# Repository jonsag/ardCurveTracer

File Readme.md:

# Transistor Curve Tracer

Based on a project I found at [instructables](https://www.instructables.com/Transistor-Curve-Tracer)

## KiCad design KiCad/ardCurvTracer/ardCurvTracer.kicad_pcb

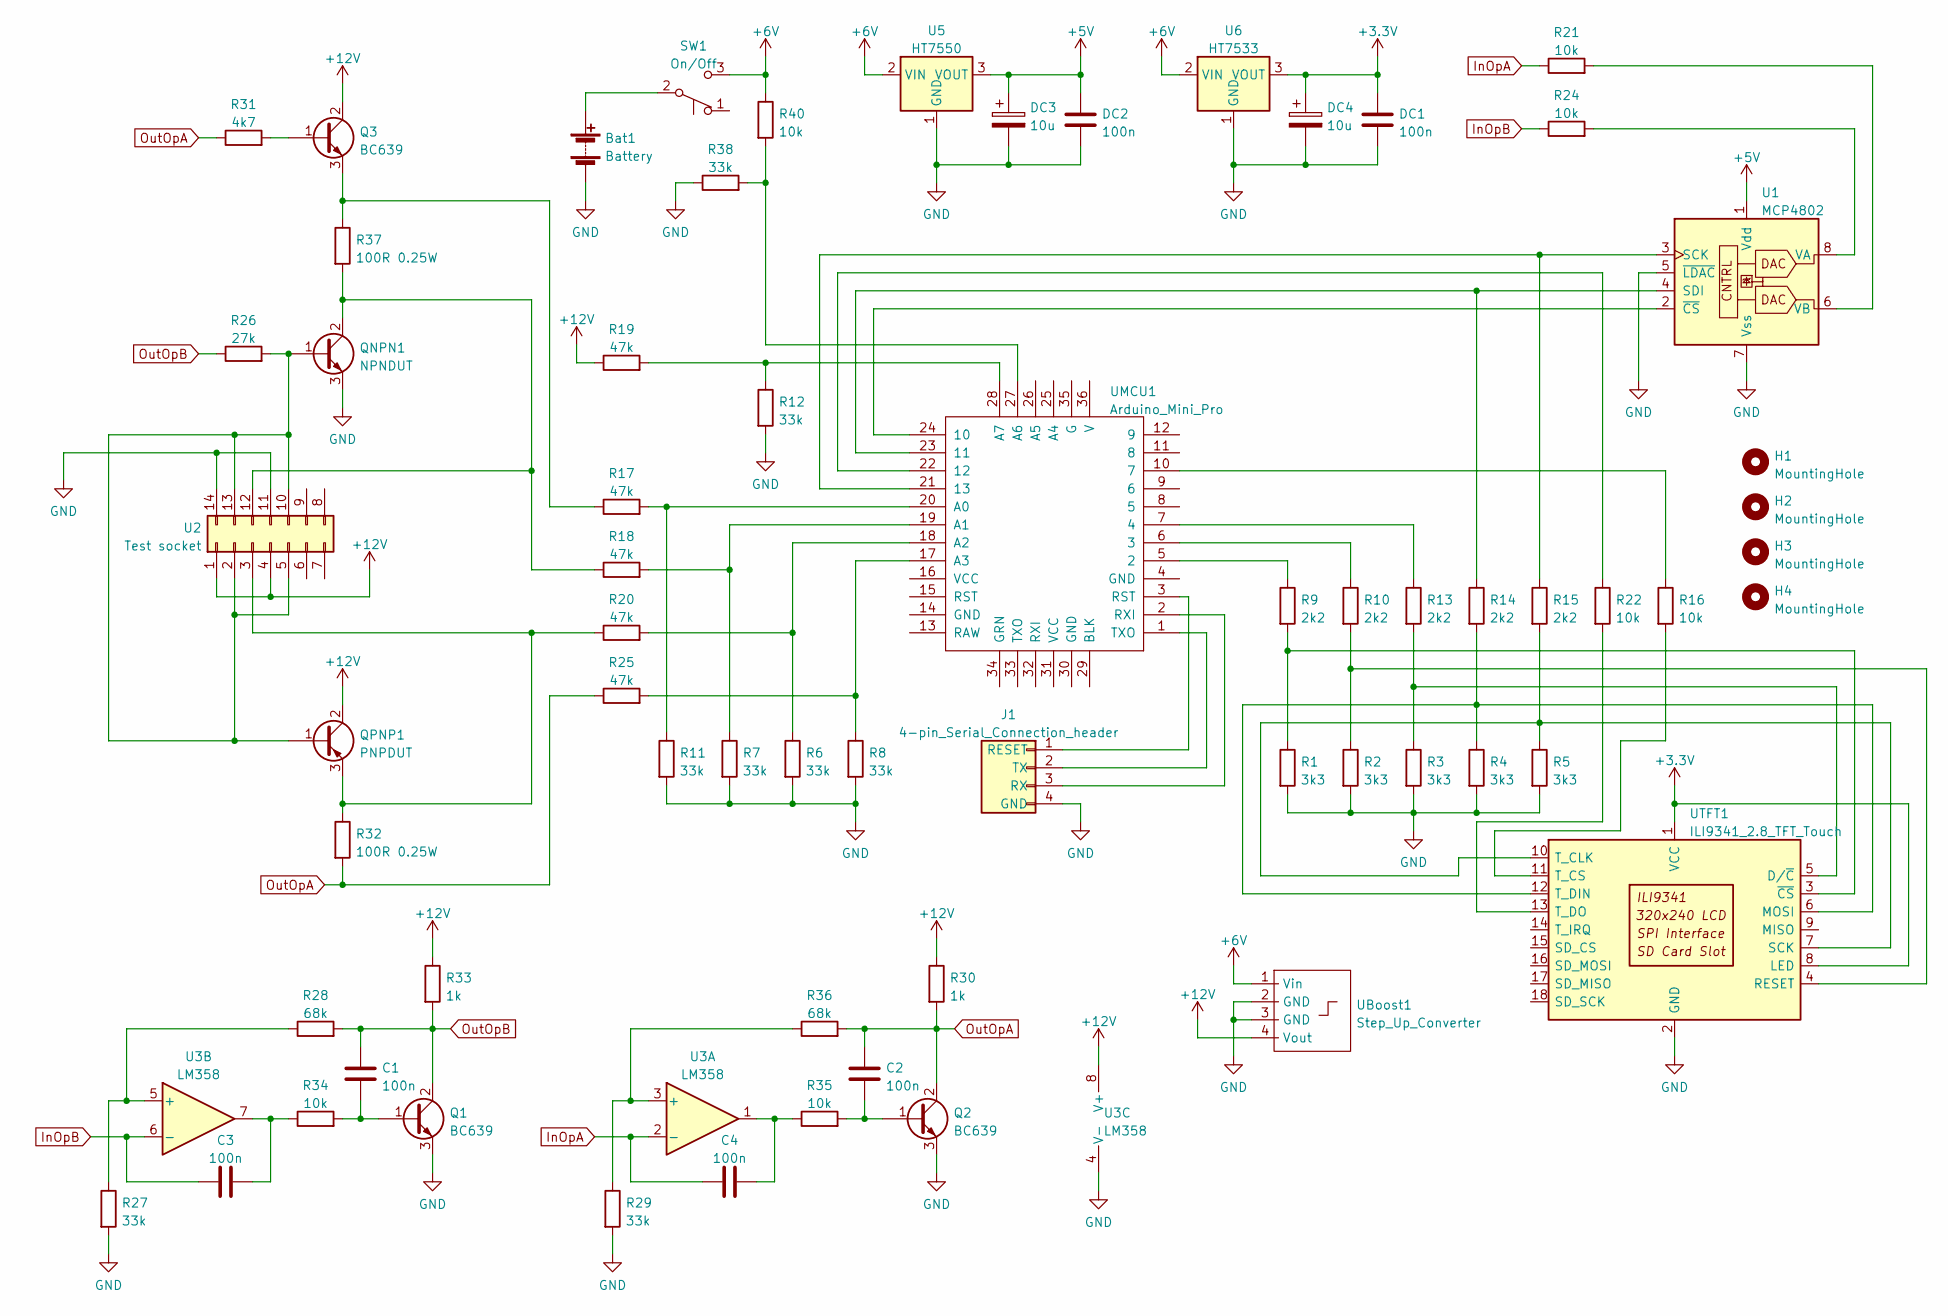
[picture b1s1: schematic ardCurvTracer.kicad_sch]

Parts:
Bat1: Battery; 2-pin_power_input_header_larger_pads
C1, C2, C3, C4: 100n; C_Disc_D3.0mm_W1.6mm_P2.50mm_larg
DC1, DC2: 100n; C_Disc_D3.0mm_W1.6mm_P2.50mm_larg
DC3, DC4: 10u; CP_Radial_D5.0mm_P2.00mm_larger
H1, H2, H3, H4: MountingHole; MountingHole_3.2mm_M3
J1: 4-pin_Serial_Connection_header; 4-pin Serial Connection header large
Q1, Q2, Q3: BC639; TO-92_Inline_Wide_large
QNPN1: NPNDUT
QPNP1: PNPDUT
R1, R2, R3, R4, R5: 3k3; R_Axial_DIN0207_L6.3mm_D2.5mm_P10.16mm_Horizontal_larger_pa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
R6, R7, R8, R11, R12, R27, R29, R38: 33k; R_Axial_DIN0207_L6.3mm_D2.5mm_P10.16mm_Horizontal_larger_pa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
R9, R10, R13, R14, R15: 2k2; R_Axial_DIN0207_L6.3mm_D2.5mm_P10.16mm_Horizontal_larger_pa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
R16, R21, R22, R24, R34, R35, R40: 10k; R_Axial_DIN0207_L6.3mm_D2.5mm_P10.16mm_Horizontal_larger_pa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
R17, R18, R19, R20, R25: 47k; R_Axial_DIN0207_L6.3mm_D2.5mm_P10.16mm_Horizontal_larger_pa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
R26: 27k; R_Axial_DIN0207_L6.3mm_D2.5mm_P10.16mm_Horizontal_larger_pa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
R28, R36: 68k; R_Axial_DIN0207_L6.3mm_D2.5mm_P10.16mm_Horizontal_larger_pa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
R30, R33: 1k; R_Axial_DIN0207_L6.3mm_D2.5mm_P10.16mm_Horizontal_larger_pa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
R31: 4k7; R_Axial_DIN0207_L6.3mm_D2.5mm_P10.16mm_Horizontal_larger_pa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
R32, R37: 100R 0.25W; R_Axial_DIN0207_L6.3mm_D2.5mm_P10.16mm_Horizontal_larger_pa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
SW1: On/Off; 2-pole switch large
U1: MCP4802; DIP-8_W7.62mm_Socket_w_dip_packet_LongPads
U2: Test socket; ZIF_DIP_Socket-14_W4.3_W5.08_W7.62_W10.16_W10.9_3M_214-3339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
U3: LM358; DIP-8_W7.62mm_Socket_w_dip_packet_LongPads
U5: HT7550; SOT-89-3
U6: HT7533; SOT-89-3
UBoost1: Step_Up_Converter; 6V to 12V Step Up Converter
UMCU1: Arduino_Mini_Pro; Arduino_Pro_Mini_vA_sides_n_A4-A7_large
UTFT1: ILI9341_2.8_TFT_Touch; ILI9341 2.8 TFT Touch large

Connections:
+3V3: DC1.1, DC4.1, U6.3 (VOUT), UTFT1.1 (VCC), UTFT1.8 (LED)
+5V: DC2.1, DC3.1, U1.1 (Vdd), U5.3 (VOUT)
+6V: R40.1, SW1.3 (C), U5.2 (VIN), U6.2 (VIN), UBoost1.1 (Vin)
+12V: Q3.2 (C), QPNP1.2 (C), R19.1, R30.1, R33.1, U2.1, U2.4, U3.8 (V+), UBoost1.4 (Vout)
GND: Bat1.2 (-), DC1.2, DC2.2, DC3.2, DC4.2, J1.4 (GND), Q1.3 (E), Q2.3 (E), QNPN1.3 (E), R1.2, R2.2, R3.2, R4.2, R5.2, R6.2, R7.2, R8.2, R11.2, R12.2, R27.2, R29.2, R38.1, U1.5 (~LDAC), U1.7 (Vss), U2.11, U2.14, U3.4 (V-), U5.1 (GND), U6.1 (GND), UBoost1.2 (GND), UBoost1.3 (GND), UTFT1.2 (GND)
InOpA: C4.1, R21.1, U3.2 (-)
InOpB: C3.1, R24.1, U3.6 (-)
unnamed: Bat1.1 (+), SW1.2 (B)
unnamed: C1.1, Q1.1 (B), R34.2
unnamed: C2.1, Q2.1 (B), R35.2
unnamed: C3.2, R34.1, U3.7
unnamed: C4.2, R35.1, U3.1
unnamed: J1.1 (RESET), UMCU1.3 (RST)
unnamed: J1.2 (TX), UMCU1.1 (TXO)
unnamed: J1.3 (RX), UMCU1.2 (RXI)
unnamed: Q3.1 (B), R31.2
unnamed: Q3.3 (E), R17.1, R37.1
unnamed: QNPN1.1 (B), QPNP1.1 (B), R26.2, U2.2, U2.5, U2.10, U2.13
unnamed: QNPN1.2 (C), R18.1, R37.2, U2.12
unnamed: QPNP1.3 (E), R20.1, R32.1, U2.3
unnamed: R1.1, R9.2, UTFT1.3 (~CS)
unnamed: R9.1, UMCU1.5 (2)
unnamed: R10.1, UMCU1.6 (3)
unnamed: R2.1, R10.2, UTFT1.4 (RESET)
unnamed: R11.1, R17.2, UMCU1.20 (A0)
unnamed: R12.1, R19.2, UMCU1.28 (A7)
unnamed: R13.1, UMCU1.7 (4)
unnamed: R3.1, R13.2, UTFT1.5 (D/~C)
unnamed: R14.1, U1.4 (SDI), UMCU1.23 (11)
unnamed: R4.1, R14.2, UTFT1.6 (MOSI), UTFT1.12 (T_DIN)
unnamed: R15.1, U1.3 (SCK), UMCU1.21 (13)
unnamed: R5.1, R15.2, UTFT1.7 (SCK), UTFT1.10 (T_CLK)
unnamed: R16.1, UMCU1.10 (7)
unnamed: R16.2, UTFT1.11 (T_CS)
unnamed: R7.1, R18.2, UMCU1.19 (A1)
unnamed: R6.1, R20.2, UMCU1.18 (A2)
unnamed: R21.2, U1.6 (VB)
unnamed: R22.1, UMCU1.22 (12)
unnamed: R22.2, UTFT1.13 (T_DO)
unnamed: R24.2, U1.8 (VA)
unnamed: R8.1, R25.2, UMCU1.17 (A3)
unnamed: R27.1, R28.1, U3.5 (+)
unnamed: R29.1, R36.1, U3.3 (+)
unnamed: R38.2, R40.2, UMCU1.27 (A6)
unnamed: U1.2 (~CS), UMCU1.24 (10)
OutOpA: C2.2, Q2.2 (C), R25.1, R30.2, R31.1, R32.2, R36.2
OutOpB: C1.2, Q1.2 (C), R26.1, R28.2, R33.2

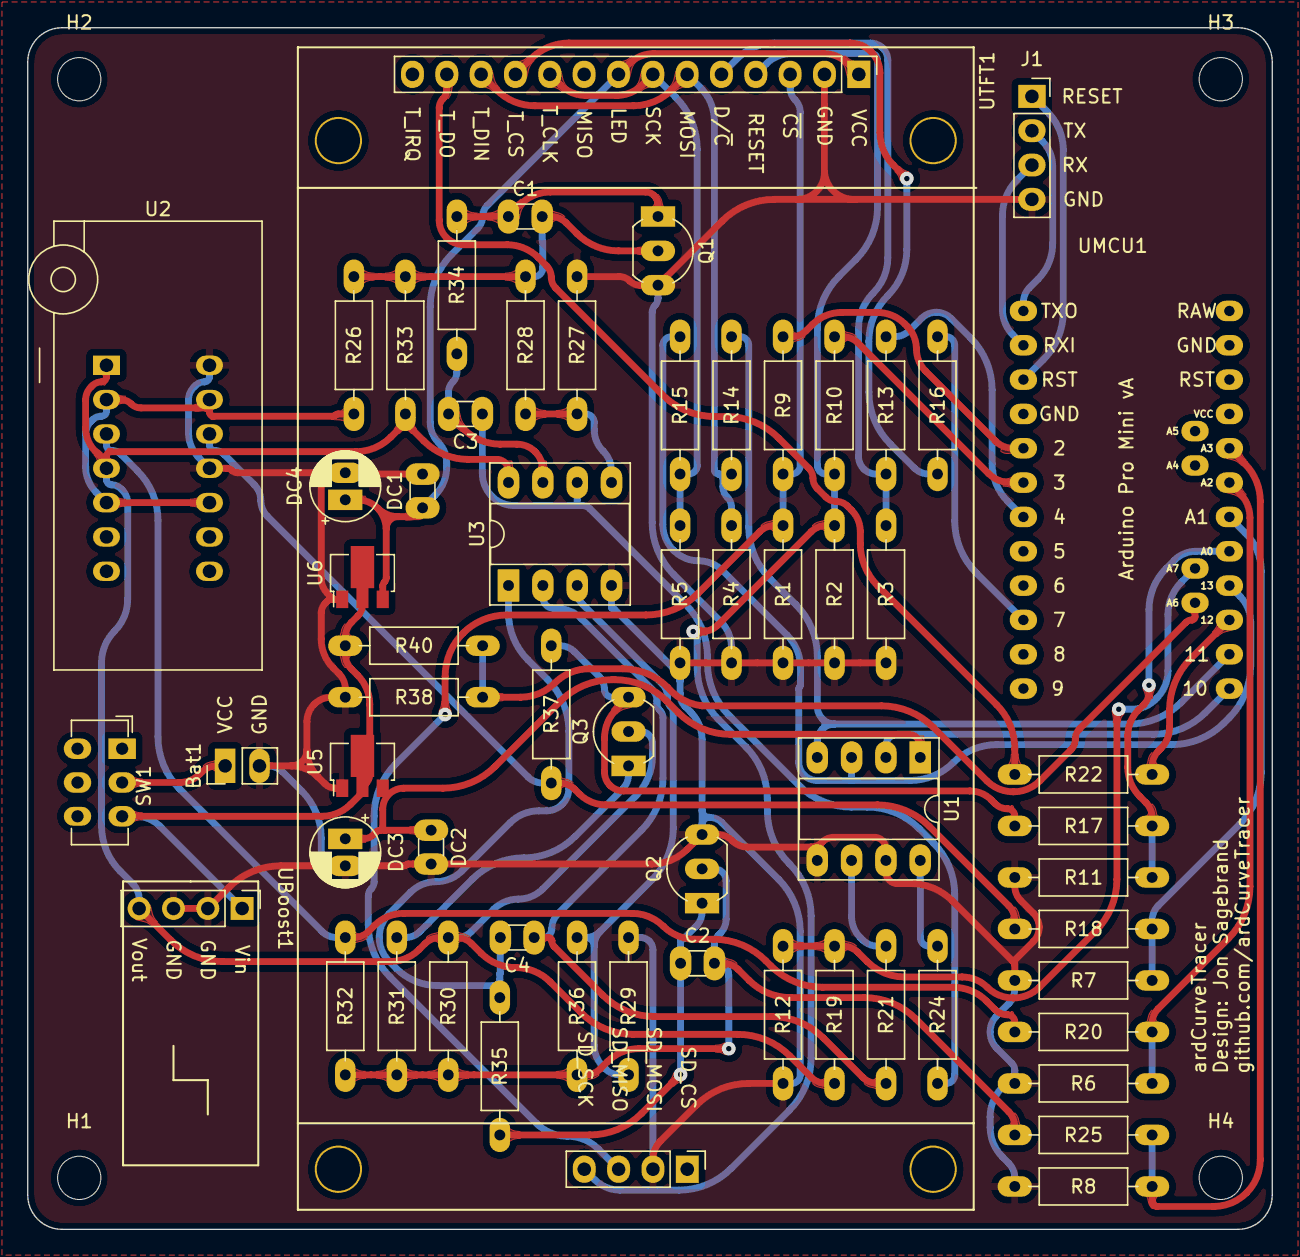
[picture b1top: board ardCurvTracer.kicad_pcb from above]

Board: 2 copper layers, 92.1 x 88.9 mm, 64 parts (0 on the bottom side), 47 nets.

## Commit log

2022-04-27 code
2022-04-27 language
2022-04-27 converter
2022-06-03 kicad
2023-02-21 kicad7
